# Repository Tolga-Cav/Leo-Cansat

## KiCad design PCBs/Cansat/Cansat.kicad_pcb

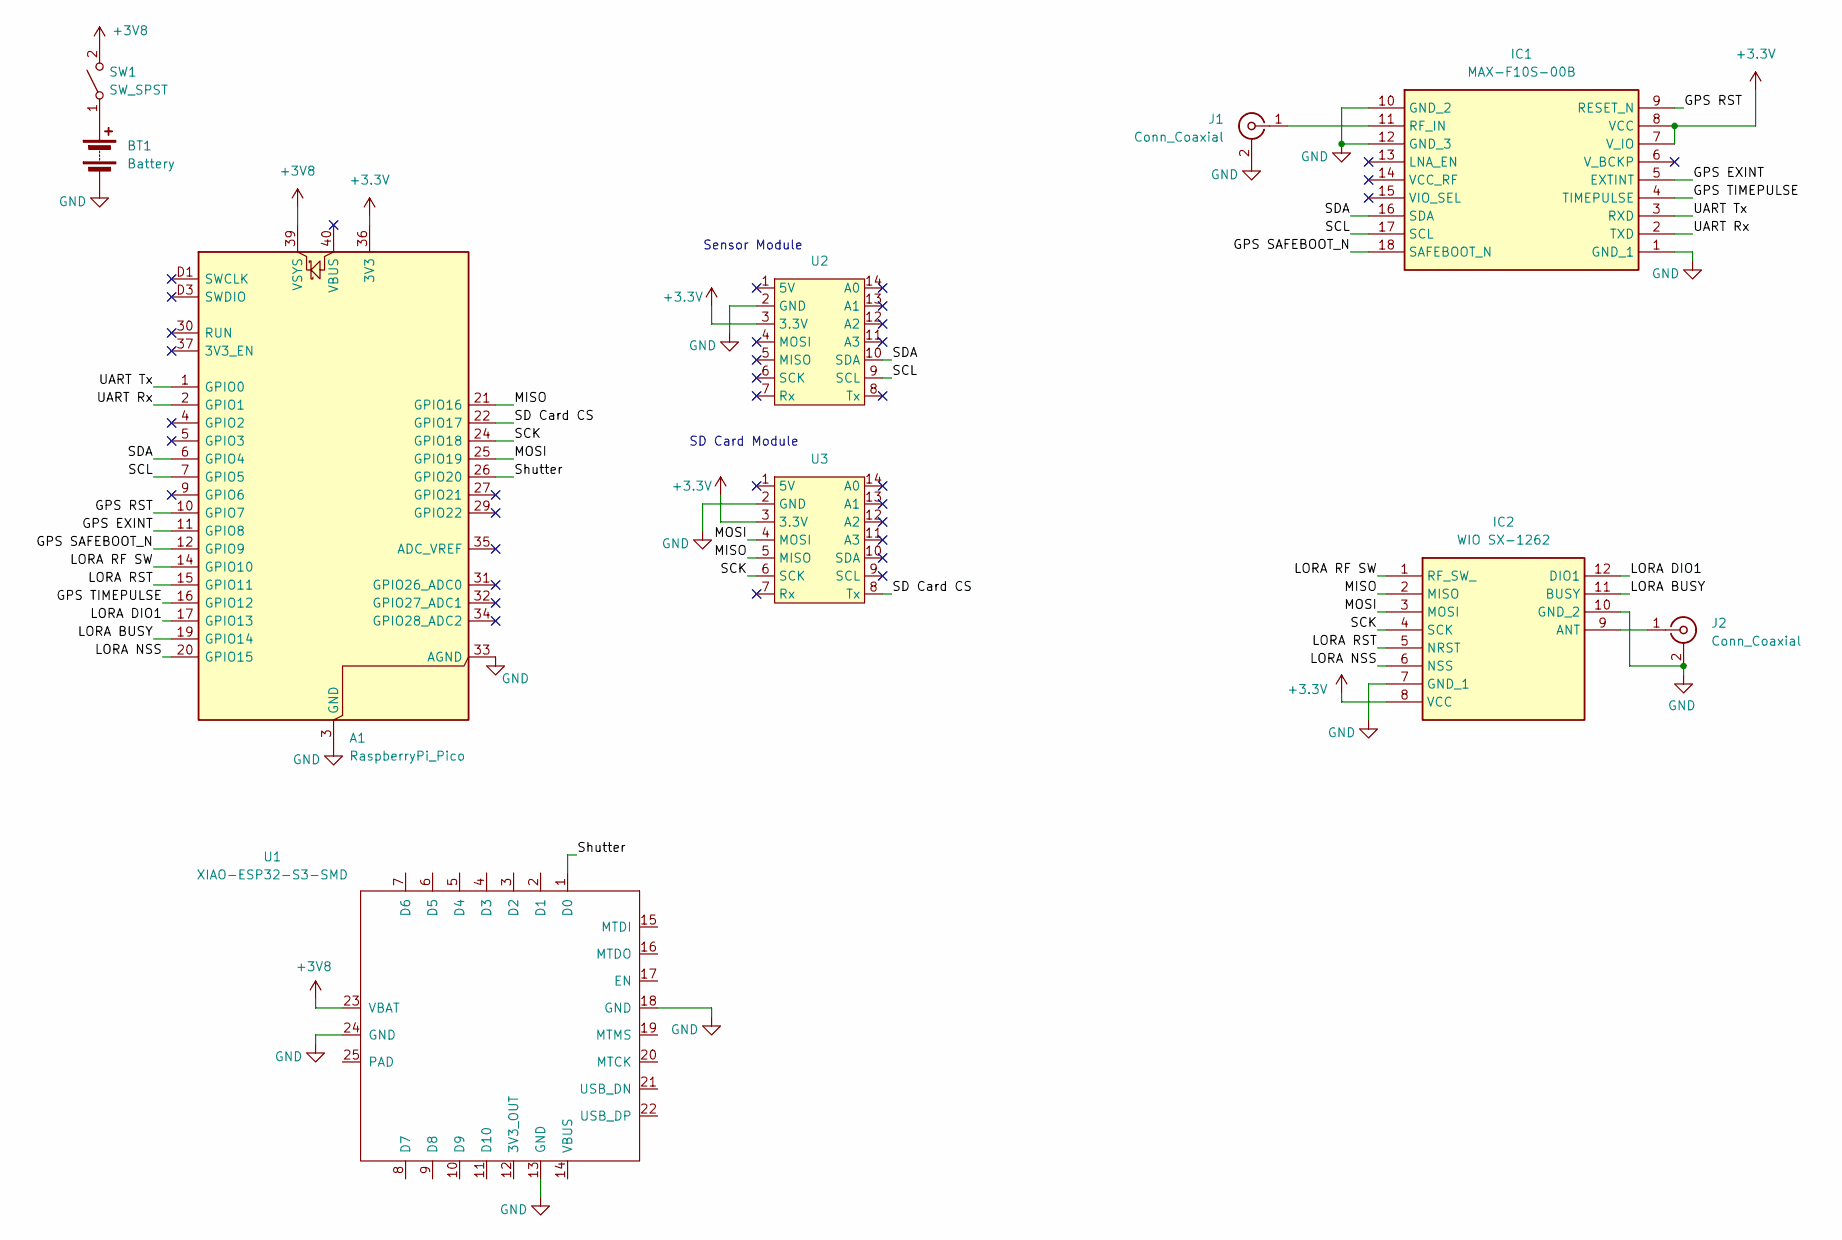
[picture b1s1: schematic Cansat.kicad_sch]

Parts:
A1: RaspberryPi_Pico; RaspberryPi_Pico_SMD_HandSolder
BT1: Battery; JST_PH_B2B-PH-K_1x02_P2.00mm_Vertical
IC1: MAX-F10S-00B; MAXF10S00B; Mouser Part Number 377-MAX-F10S-00B
IC2: WIO SX-1262; wio sx1262; Mouser Part Number 713-114993390
J1: Conn_Coaxial; HIROSE_U.FL-R-SMT_10_
J2: Conn_Coaxial; RFSOLUTIONS_CON-SMA-EDGE-S
SW1: SW_SPST; PinHeader_1x02_P2.54mm_Vertical
U1: XIAO-ESP32-S3-SMD
U2: Sensor BFF
U3: Microsd BFF

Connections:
+3.3V: A1.36 (3V3), IC1.7 (V_IO), IC1.8 (VCC), IC2.8 (VCC), U2.3 (3.3V), U3.3 (3.3V)
+3V8: A1.39 (VSYS), SW1.2 (B), U1.23 (VBAT)
/GPS EXINT: A1.11 (GPIO8), IC1.5 (EXTINT)
/GPS RST: A1.10 (GPIO7), IC1.9 (RESET_N)
/GPS SAFEBOOT_N: A1.12 (GPIO9), IC1.18 (SAFEBOOT_N)
/GPS TIMEPULSE: A1.16 (GPIO12), IC1.4 (TIMEPULSE)
/LORA BUSY: A1.19 (GPIO14), IC2.11 (BUSY)
/LORA DIO1: A1.17 (GPIO13), IC2.12 (DIO1)
/LORA NSS: A1.20 (GPIO15), IC2.6 (NSS)
/LORA RF SW: A1.14 (GPIO10), IC2.1 (RF_SW_)
/LORA RST: A1.15 (GPIO11), IC2.5 (NRST)
/MISO: A1.21 (GPIO16), IC2.2 (MISO), U3.5 (MISO)
/MOSI: A1.25 (GPIO19), IC2.3 (MOSI), U3.4 (MOSI)
/SCK: A1.24 (GPIO18), IC2.4 (SCK), U3.6 (SCK)
/SCL: A1.7 (GPIO5), IC1.17 (SCL), U2.9 (SCL)
/SD Card CS: A1.22 (GPIO17), U3.8 (Tx)
/SDA: A1.6 (GPIO4), IC1.16 (SDA), U2.10 (SDA)
/Shutter: A1.26 (GPIO20), U1.1 (D0)
/UART Rx: A1.2 (GPIO1), IC1.2 (TXD)
/UART Tx: A1.1 (GPIO0), IC1.3 (RXD)
GND: A1.3 (GND), A1.8 (GND), A1.13 (GND), A1.18 (GND), A1.23 (GND), A1.28 (GND), A1.33 (AGND), A1.38 (GND), A1.D2 (GND), BT1.2 (-), IC1.1 (GND_1), IC1.10 (GND_2), IC1.12 (GND_3), IC2.7 (GND_1), IC2.10 (GND_2), J1.2 (Ext), J2.2 (Ext), U1.13 (GND), U1.18 (GND), U1.24 (GND), U2.2 (GND), U3.2 (GND)
unnamed: BT1.1 (+), SW1.1 (A)
unnamed: IC1.11 (RF_IN), J1.1 (In)
unnamed: IC2.9 (ANT), J2.1 (In)

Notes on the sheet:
Sensor Module
SD Card Module

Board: 2 copper layers, 10 parts (3 on the bottom side), 24 nets, no tracks yet.

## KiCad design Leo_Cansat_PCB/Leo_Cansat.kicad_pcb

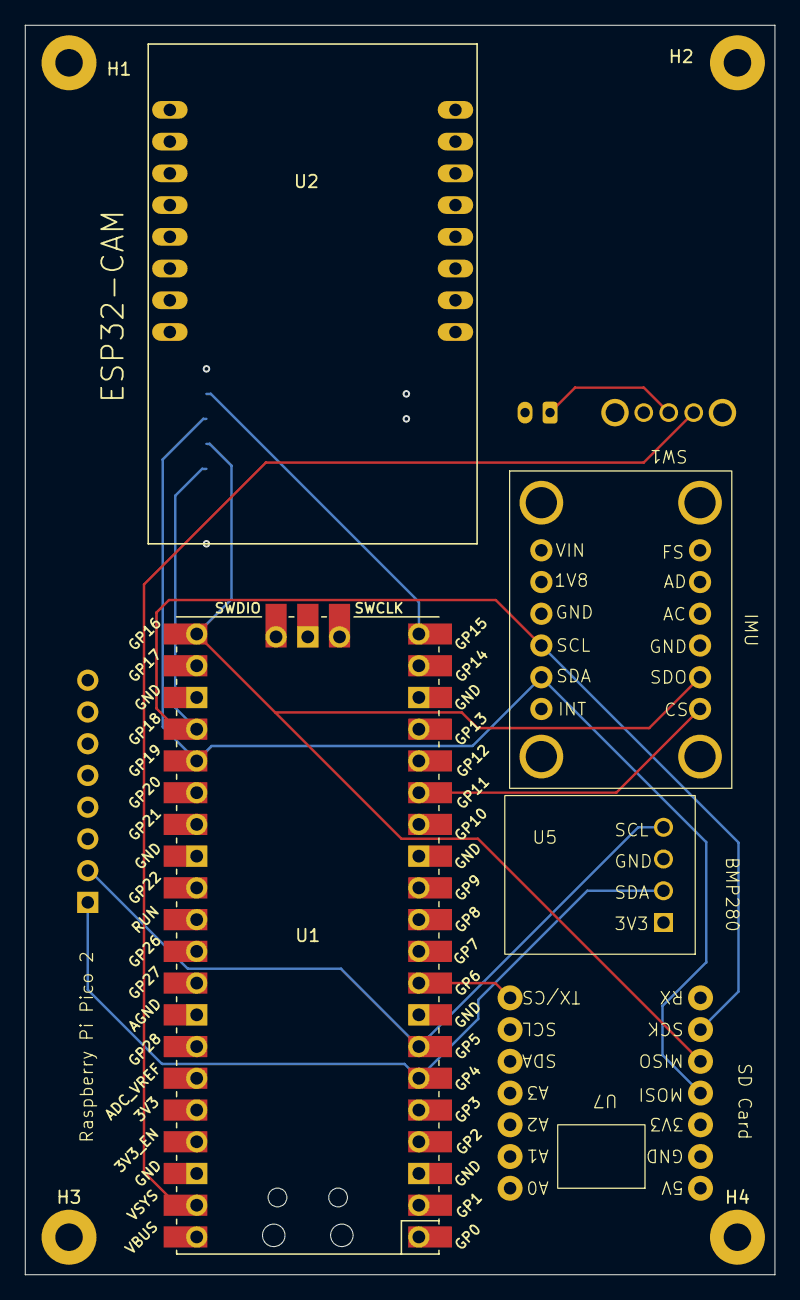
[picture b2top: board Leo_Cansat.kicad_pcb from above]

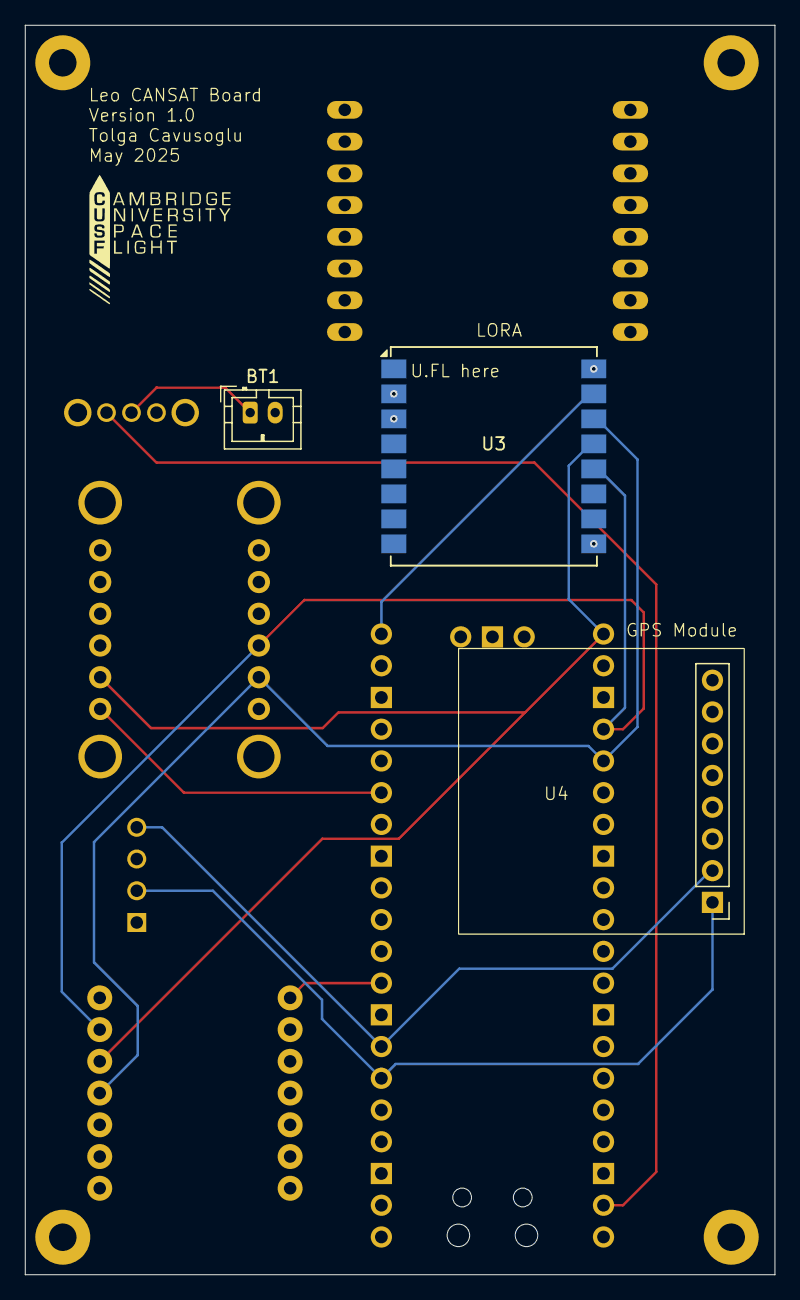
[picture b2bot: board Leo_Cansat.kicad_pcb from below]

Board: 4 copper layers, 60.0 x 100.0 mm, 13 parts (3 on the bottom side), 12 nets.

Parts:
BT1: Battery_Cell; JST_PH_B2B-PH-K_1x02_P2.00mm_Vertical
H1, H2, H3, H4: MountingHole_Pad; MountingHole_2.2mm_M2_Pad
SW1: SW_SPDT; SK-12D07
U1: Pico; RPi_Pico_SMD_TH
U2: ESP32-CAM
U3: Ai-Thinker-Ra-01; Ai-Thinker-Ra-01-LoRa
U4: MAX-M8Q-0-10 breakout board
U5: AHT20+BMP280
U6: ICM20948
U7: BFF SD Card

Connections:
+3V3: U1.36 (3V3), U2.P$16 (3V3), U3.3 (VDD), U4.8 (VCC), U5.4 (VCC), U6.7 (VIN), U7.3 (3V3)
/IMUCS: U1.15 (GPIO11), U6.1 (CS)
/LORACS: U1.20 (GPIO15), U3.15 (~NSS)
/MISO: U1.21 (GPIO16), U3.13 (MISO), U6.2 (SDO), U7.5 (MISO)
/MOSI: U1.25 (GPIO19), U3.14 (MOSI), U6.11 (SDA), U7.4 (MOSI)
/SCK: U1.24 (GPIO18), U3.12 (SCK), U6.10 (SCL), U7.6 (SCK)
/SCL: U1.7 (GPIO5), U4.2 (SCL), U5.1 (SCL)
/SDA: U1.6 (GPIO4), U4.1 (SDA), U5.3 (SDA)
/SDCS: U1.9 (GPIO6), U7.14 (CS)
GND: BT1.2 (-), H1.1, H2.1, H3.1, H4.1, U1.3 (GND), U1.8 (GND), U1.13 (GND), U1.18 (GND), U1.23 (GND), U1.28 (GND), U1.38 (GND), U1.42 (GND), U2.P$2 (GND), U3.2 (GND), U3.9 (GND), U3.16 (GND), U4.7 (GND), U5.2 (GND), U6.3 (GND), U7.2 (GND)
unnamed: BT1.1 (+), SW1.2 (B)
unnamed: SW1.1 (A), U1.39 (VSYS)

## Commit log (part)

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2025-06-21 Initial Commit
    First addition of all files to the repository.
2025-06-29 Updated GPS test code to reflect UART
2025-10-12 Some small cad changes
2025-10-17 CAD Updates
2025-10-26 Fixed uart Pins on GPS Test code
2025-11-16 Lora Testing
2025-11-16 Added Lora Library
2025-11-16 Correct Lora Library
2025-11-16 Lora configuration test
2025-11-23 Further LoRa Testing
2026-02-02 Implement ESP-32 Camera Test
2026-02-22 Fix pin definitions in library
2026-02-22 Finalize ESP 32 Cam code
2026-03-14 Started main code loop for cansat
2026-03-15 Minor Edits
